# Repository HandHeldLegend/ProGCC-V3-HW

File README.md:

# ProGCC V3 HW
This is the official Github page for the ProGCC V3 hardware from Hand Held Legend.

## PCB Design License
<br />This PCB design (includes the layout of traces, footprints, and PCB board layout) is licensed under a <a rel="license" href="http://creativecommons.org/licenses/by-nc-sa/3.0/">Creative Commons Attribution-NonCommercial-ShareAlike 3.0 Unported License</a>.

## PCB Schematic License
This PCB schematic is licensed under a <a rel="license" href="https://ohwr.org/cern_ohl_s_v2.pdf">CERN-OHL-S Strongly Reciprocal License</a>.<br>
It contains elements derived from [PhobGCC Hardware](https://github.com/PhobGCC/PhobGCC-HW/) including the rumble schematic and choice of ADCs.

## Shop Links
- [TBA](https://handheldlegend.com)

## Detailed Information
All of our guides on assembly, updating the firmware, and operation
are listed on [our Wiki page linked here](https://wiki.handheldlegend.com).

## Features
- TBA

## Attributions
- Partial trace layout work and initial prototyping performed by [Esca](https://github.com/ESCA47/).
- Main PCB, button board PCB, and bulk schematic designed by Mitch Cairns.
- Rumble schematic derived from work created by the [PhobGCC Team](https://github.com/PhobGCC/).

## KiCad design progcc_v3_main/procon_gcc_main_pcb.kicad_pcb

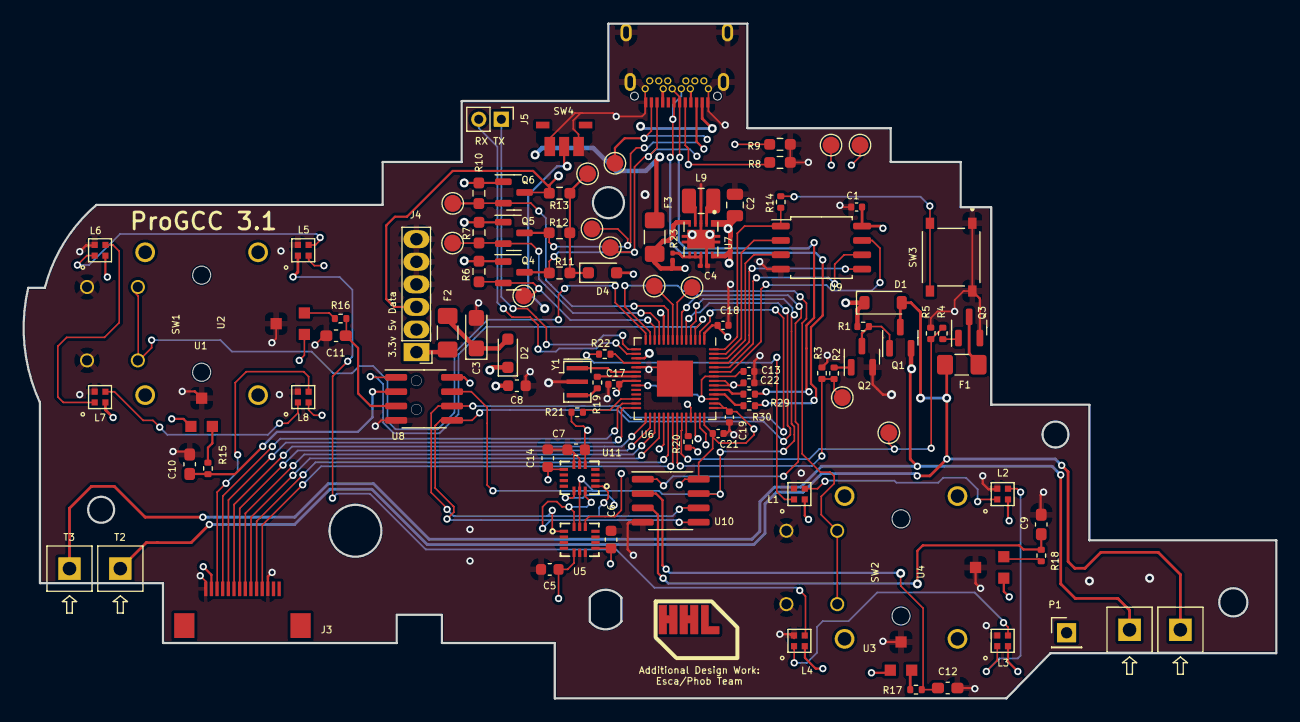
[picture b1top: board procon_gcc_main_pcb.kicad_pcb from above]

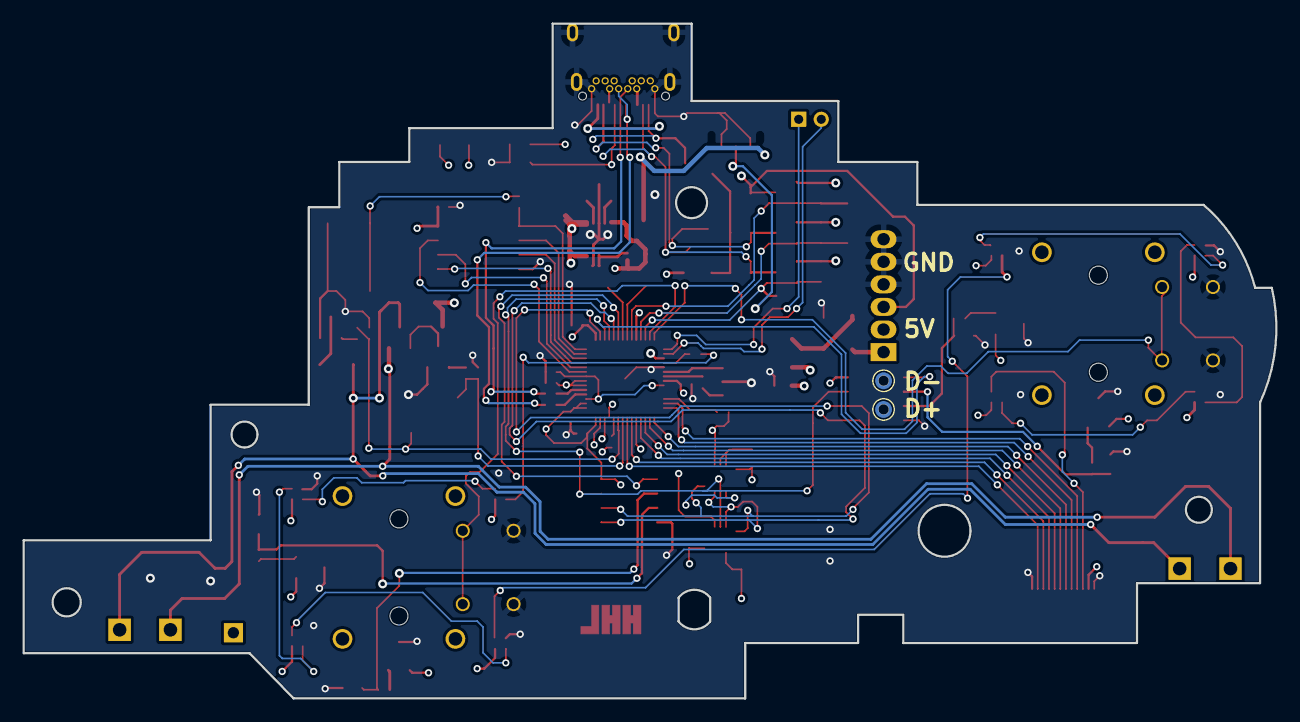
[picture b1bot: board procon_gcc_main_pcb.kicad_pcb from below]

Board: 4 copper layers, 110.9 x 59.7 mm, 105 parts (2 on the bottom side), 84 nets.

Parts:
C1, C13, C17, C18, C21, C22: 100n; C_0402_1005Metric
C2: 10uF; C_0805_2012Metric
C3: 47uF 6.3v; CP_EIA-3216-18_Kemet-A
C4: 100n; C_0201_0603Metric
C5, C6, C7, C14: 100nF; C_0603_1608Metric
C8: 10u; C_0603_1608Metric
C9, C10, C11, C12: .047u; C_0603_1608Metric_Pad1.08x0.95mm_HandSolder
C19: 1u; C_0402_1005Metric
D1: M7C; D_SOD-123
D2, D4: CUS08F30; D_SOD-323_HandSoldering
F1, F2, F3: Fuse; Fuse_1206_3216Metric_Pad1.42x1.75mm_HandSolder
J3: To Button Board; molex_5051101492_14P
J4: Conn_01x06_Female; GCC_Header_Straight_1x06_Pitch2.00mm
J5: Conn_01x02_Pin; PinHeader_1x02_P2.00mm_Vertical
J9: USB_C_Receptacle; Shou Han Type-C 24P QCHT
L1, L2, L3, L4, L5, L6, L7, L8: SK6805-EC-15
L9: 1.3A 2.2uH ±20% 80mΩ; L_1008_2520Metric
P1: Endpoint; PinHeader_1x01_P2.54mm_Vertical
Q1: Q_PMOS_GDS; SOT-23
Q2, Q3: Q_NMOS_GSD; SOT-23
Q4, Q5, Q6: BSS138; SOT-23
R1, R3, R5, R21: 10k; R_0402_1005Metric
R2, R4: 100R; R_0402_1005Metric
R6, R7, R10, R11, R12, R13: 1k; R_0603_1608Metric_Pad0.98x0.95mm_HandSolder
R8, R9: 5.1k; R_0603_1608Metric_Pad0.98x0.95mm_HandSolder
R14, R15, R16, R17, R18, R19: 1k; R_0402_1005Metric
R20: 500K; R_0402_1005Metric
R22: 330; R_0402_1005Metric
R23: 100; R_0201_0603Metric
R29, R30: 27; R_0402_1005Metric
SW1, SW2: GL18_SW; GL18
SW3: TS-1187A-B-A-B; SW_TS-1187A-B-A-B
SW4: TS35CA
T1, T2, T3, T4: 36-8730; KS_8730
TP1, TP2, TP3, TP4, TP5, TP6, TP7, TP8, TP9, TP10, TP11, TP12, TP14, TP15, TP16: TestPoint; TestPoint_Pad_D1.5mm
U1, U2, U3, U4: GH39F (Hall SOT23); GH39F
U5, U11: ST_LSM6; LGA14
U6: RP2040; QFN-56-1EP_7x7mm_P0.4mm_EP3.2x3.2mm
U7: TPS630001RCR; VREG_V62_16624-01YE
U8, U10: MCP3002; SOIC-8_3.9x4.9mm_P1.27mm
U9: W25Q128JVS; SOIC-8_5.23x5.23mm_P1.27mm
Y1: Crystal_GND3; Resonator_SMD_Murata_CSTxExxV-3Pin_3.0x1.1mm

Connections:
+1V1: C13.2, U6.23 (DVDD), U6.45 (VREG_VOUT), U6.50 (DVDD)
+3.3V_PRE: F2.1, J4.1, J9.A2 (TX1+), J9.B2 (TX2+)
+3V3: C1.1, C2.1, C5.2, C6.2, C7.2, C8.2, C14.2, C17.1, C18.1, C19.1, C21.2, C22.2, D4.2 (A), J3.2, L1.2 (VDD), L2.2 (VDD), L3.2 (VDD), L4.2 (VDD), L5.2 (VDD), L6.2 (VDD), L7.2 (VDD), L8.2 (VDD), Q4.1 (G), Q5.1 (G), Q6.1 (G), R6.1, R7.1, R10.1, R21.1, TP14.1, U1.1 (VDD), U2.1 (VDD), U3.1 (VDD), U4.1 (VDD), U5.5 (VDDIO), U5.8 (VDD), U6.1 (IOVDD), U6.10 (IOVDD), U6.22 (IOVDD), U6.33 (IOVDD), U6.42 (IOVDD), U6.43 (ADC_AVDD), U6.44 (VREG_IN), U6.48 (USB_VDD), U6.49 (IOVDD), U7.1 (VOUT), U7.10 (FB), U8.8 (VDD/VREF), U9.8 (VCC), U10.8 (VDD/VREF), U11.5 (VDDIO), U11.8 (VDD)
+5V_PRE: F3.1, J4.2, J9.A4 (VBUS), J9.A9 (VBUS), J9.B4 (VBUS), J9.B9 (VBUS)
+VCC: D1.1 (K), D2.1 (K), F3.2, Q1.2 (S), R1.2, R23.1, T1.1, T3.1, TP9.1, U7.5 (VIN)
/CC1: J9.A5 (CC1), R8.1
/CC2: J9.B5 (CC2), R9.1
/QSPI_SCLK: U6.52 (QSPI_SCLK), U9.6 (CLK)
/QSPI_SD0: U6.53 (QSPI_SD0), U9.5 (DI(IO0))
/QSPI_SD1: U6.55 (QSPI_SD1), U9.2 (DO(IO1))
/QSPI_SD2: U6.54 (QSPI_SD2), U9.3 (IO2)
/QSPI_SD3: U6.51 (QSPI_SD3), U9.7 (IO3)
/QSPI_SS: R14.1, U6.56 (QSPI_SS), U9.1 (~CS)
/RUN: R21.2, U6.26 (RUN)
/~USB_BOOT: R14.2, SW3.C, SW3.D
BUTTON_RGB: J3.3, L8.3 (DOUT)
D+: J9.A6 (D+), J9.B6 (D+), R29.1, TP12.1
D-: J9.A7 (D-), J9.B7 (D-), R30.1, TP10.1
GND: C1.2, C2.2, C3.2, C4.1, C5.1, C6.1, C7.1, C8.1, C9.1, C10.1, C11.1, C12.1, C13.1, C14.1, C17.2, C18.2, C19.2, C21.1, C22.1, J3.1, J3.12, J4.4, J4.5, J4.6, J9.A1 (GND), J9.A12 (GND), J9.B1 (GND), J9.B12 (GND), J9.S1 (SHIELD), L1.4 (GND), L2.4 (GND), L3.4 (GND), L4.4 (GND), L5.4 (GND), L6.4 (GND), L7.4 (GND), L8.4 (GND), Q2.2 (S), Q3.2 (S), R3.1, R5.1, R8.2, R9.2, SW1.S3 (3), SW1.S4 (4), SW2.S3 (3), SW2.S4 (4), SW3.A, SW3.B, SW4.1, SW4.3, U1.3 (GND), U2.3 (GND), U3.3 (GND), U4.3 (GND), U5.2 (SDx), U5.3 (SCx), U5.6 (GNDIO), U5.7 (GND), U6.19 (TESTEN), U6.57 (GND), U7.3 (PGND), U7.9 (GND), U7.11 (EP), U8.4 (VSS), U9.4 (GND), U10.4 (VSS), U11.2 (SDx), U11.3 (SCx), U11.6 (GNDIO), U11.7 (GND), Y1.2
GP1: TP15.1, U6.7 (GPIO5)
GP2: TP16.1, U6.8 (GPIO6)
IMU0_CS: U5.12 (CS), U6.40 (GPIO28_ADC2)
IMU1_CS: U6.41 (GPIO29_ADC3), U11.12 (CS)
LADC_CS: U6.3 (GPIO1), U8.1 (~CS/SHDN)
LS_BUTTON: SW1.S1 (1), SW1.S2 (2), U6.14 (GPIO11)
LX: C10.2, R15.2, U8.2 (CH0)
LY: C11.2, R16.2, U8.3 (CH1)
MODE_BUTTON: SW4.2, U6.17 (GPIO14)
NFC: J3.13, J3.14
N_CLOCK: J9.A3 (TX1-), J9.B3 (TX2-), Q5.3 (D), R12.2, TP6.1
N_CLOCK_3.3: Q5.2 (S), R7.2, TP2.1, U6.11 (GPIO8)
N_DATA: J4.3, J9.A11 (RX2+), J9.B11 (RX1+), Q6.3 (D), R13.2, TP7.1
N_DATA_3.3: Q6.2 (S), R10.2, TP3.1, U6.9 (GPIO7)
N_LATCH: J9.A10 (RX2-), J9.B10 (RX1-), Q4.3 (D), R11.2, TP5.1
N_LATCH_3.3: Q4.2 (S), R6.2, TP1.1, U6.12 (GPIO9)
unnamed: C3.1, D2.2 (A), F2.2
unnamed: L1.3 (DOUT), L2.1 (DIN)
unnamed: L2.3 (DOUT), L3.1 (DIN)
unnamed: L3.3 (DOUT), L4.1 (DIN)
unnamed: L5.3 (DOUT), L6.1 (DIN)
unnamed: L6.3 (DOUT), L7.1 (DIN)
unnamed: L7.3 (DOUT), L8.1 (DIN)
unnamed: Q1.1 (G), Q2.3 (D), R1.1
unnamed: Q2.1 (G), R2.2
unnamed: F1.2, Q3.3 (D)
unnamed: Q3.1 (G), R4.2
unnamed: R19.1, Y1.3
unnamed: R15.1, U1.2 (VOUT)
unnamed: R16.1, U2.2 (VOUT)
unnamed: R17.1, U3.2 (VOUT)
unnamed: R18.1, U4.2 (VOUT)
unnamed: R30.2, U6.46 (USB_DM)
unnamed: R29.2, U6.47 (USB_DP)
unnamed: C4.2, R23.2, U7.6 (EN), U7.7 (PS/SYNC), U7.8 (VINA)
unnamed: L9.1, U7.4 (L1)
unnamed: L9.2, U7.2 (L2)
Push_A: J3.4, U6.27 (GPIO16)
Push_B: J3.6, U6.29 (GPIO18)
Push_C: J3.9, U6.32 (GPIO21)
Push_D: J3.10, U6.34 (GPIO22)
RADC_CS: U6.6 (GPIO4), U10.1 (~CS/SHDN)
RGB_OUT: R22.2, U6.18 (GPIO15)
RS_BUTTON: SW2.S1 (1), SW2.S2 (2), U6.13 (GPIO10)
RUMBLE: R4.1, R5.2, TP11.1, U6.37 (GPIO25)
RUMBLE-: D1.2 (A), F1.1, Q1.3 (D), T2.1, T4.1
RX: C12.2, R17.2, U10.2 (CH0)
RY: C9.2, R18.2, U10.3 (CH1)
R_BRAKE: R2.1, R3.2, TP8.1, U6.36 (GPIO24)
SHARED_PU: D4.1 (K), R11.1, R12.1, R13.1, TP4.1
SL_RGB: L1.1 (DIN), R22.1
SPI_CK: U5.13 (SCL), U6.4 (GPIO2), U8.7 (CLK), U10.7 (CLK), U11.13 (SCL)
SPI_RX: U5.1 (SDO), U6.2 (GPIO0), U8.6 (DOUT), U10.6 (DOUT), U11.1 (SDO)
SPI_TX: U5.14 (SDA), U6.5 (GPIO3), U8.5 (DIN), U10.5 (DIN), U11.14 (SDA)
SR_RGB: L4.3 (DOUT), L5.1 (DIN)
Scan_A: J3.11, U6.35 (GPIO23)
Scan_B: J3.8, U6.31 (GPIO20)
Scan_C: J3.5, U6.28 (GPIO17)
Scan_D: J3.7, U6.30 (GPIO19)
TOUCH_IN: R20.1, U6.38 (GPIO26_ADC0)
TOUCH_OUT: P1.1, R20.2, U6.39 (GPIO27_ADC1)
UART0_RX: J5.2, U6.16 (GPIO13)
UART0_TX: J5.1, U6.15 (GPIO12)
XTAL_IN: U6.20 (XIN), Y1.1
XTAL_OUT: R19.2, U6.21 (XOUT)

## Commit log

2023-07-29 Typo
2023-07-29 remove D3
2023-09-17 Fix right stick LED group
2023-12-20 Update regulator
